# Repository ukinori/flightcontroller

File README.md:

# STM32H743 VTOL Flight Controller

Custom four-layer flight-controller hardware for VTOL and fixed-wing aircraft, designed in **KiCad 10** around the **STM32H743VITx**. The intended aircraft configuration is four lift motors, one cruise motor and up to five servos. The hardware has twelve output connectors, allowing spare channels.

**Status: routed hardware prototype.** PX4 integration is planned; this repository does not contain a completed PX4 board port, bootloader or flight-tested firmware. The board has not been electrically or flight qualified. Design-rule checks do not establish functional or flight safety.

[Hardware inspection guide](docs/PROJECT-RU.md) · [Board review and bring-up checklist](docs/PROJECT-RU.md#before-fabrication-and-bring-up)

Current KiCad 3D rendering. Sensor bodies include nominal package envelopes; see [3D model notes](3d-model-notes.json).

## Hardware

- STM32H743VITx microcontroller, external 8 MHz crystal, SWD and reset/boot access.
- Two ICM-42688-P inertial sensors and one BMI088; BMP390 barometers.
- SPI FRAM and a microSD socket using SDMMC.
- USB-C USB 2.0 device interface with separate CC pull-down resistors and USB protection.
- GPS, telemetry and RC UART connectors; external I2C connectors for compass/airspeed devices.
- Battery-voltage and external current-sense inputs, status indicators, safety input and buzzer circuitry.
- Twelve signal/GND output headers; OUT7–OUT12 also carry a separately supplied servo rail.
- TPS62162DSG fixed 3.3 V buck regulator and a filtered analog supply.
- Approximate board size: 70 × 100 mm; four copper layers; nominal thickness 1.6 mm.

Exact component references, values, connections and footprints are defined by the KiCad sources. The BOM CSV files cover footprint assignments and selected power/crystal/decoupling parts; they are not a fully qualified purchasing BOM.

## Open the project

1. Download the repository or clone it with `git clone https://github.com/ukinori/flightcontroller.git`.
2. Open **flightcontroller.kicad_pro** in KiCad 10.
3. Open **flightcontroller.kicad_sch** for the schematic hierarchy and **flightcontroller.kicad_pcb** for the routed board.
4. Install the standard KiCad symbol and footprint libraries. Project-specific libraries are bundled in **FlightController.kicad_sym** and **FlightController.pretty/** and use `${KIPRJMOD}` paths.
5. In PCB Editor, press **Alt+3** to open the 3D Viewer. Keep `models/` beside the project and install the standard KiCad 3D model libraries.
6. Refill copper zones and rerun ERC/DRC after making changes.

The root schematic contains MCU, power and interface sheets. The MCU sheet is currently named **untitled.kicad_sch**; this file is required by the hierarchy.

## Power connections

- **J4:** regulated **5 V input** for the controller; pin 1 is +5V and pin 2 is GND.
- The intended 6–12S aircraft battery requires a **separate external regulator**. Do not connect raw pack voltage to J4.
- USB VBUS and the external supply feed the controller input through diode paths; the onboard converter produces 3.3 V.
- **J22:** separate regulated **6 V servo supply**; pin 1 is VCC_SERVO and pin 2 is GND. The connector footprint is Phoenix Contact **1715721**.
- Controller and servo grounds are common. Servo power is independent of the 3.3 V logic supply.

The servo distribution has a provisional 10 A aggregate design target, **not a verified current rating**. Select actual servos, calculate combined stall/peak current and validate the BEC, connector, wiring, copper thickness, voltage drop and temperature rise before use. Servos/ESCs must accept the controller's signal levels.

## Output mapping

Every output header uses pin 1 for signal and pin 3 for GND. Pin 2 is unconnected on OUT1–OUT6; on OUT7–OUT12 it is VCC_SERVO.

- OUT1 — J11 — PE9, through R31.
- OUT2 — J10 — PE11, through R33.
- OUT3 — J9 — PE13, through R30.
- OUT4 — J6 — PE14, through R27.
- OUT5 — J5 — PC6, through R26.
- OUT6 — J7 — PC7, through R35.
- OUT7 — J8 — PD12, through R32.
- OUT8 — J12 — PD13, through R28.
- OUT9 — J13 — PD14, through R34.
- OUT10 — J16 — PD15, through R25.
- OUT11 — J15 — PA0, through R29.
- OUT12 — J14 — PA1, through R24.

The intended allocation is OUT1–OUT5 for five DShot ESCs, OUT7–OUT11 for five PWM servos, and OUT6/OUT12 as spares. Timer, DMA and output-mode support still need implementation and testing in a dedicated PX4 board port.

## Other connectors

See the [JST-GH wiring guide](README-JST-GH.md) and [connector BOM](JST-GH-CONNECTORS.csv) before making cables.

- **J1 SWD (custom 5-pin GH):** pin 1 SWDIO, pin 2 SWCLK, pin 3 NRST, pin 4 3.3 V reference, pin 5 GND.
- **J18 GPS (6-pin GH, Pixhawk GPS2 signal order):** pin 1 +5V, pin 2 controller TX, pin 3 controller RX, pin 4 SCL, pin 5 SDA, pin 6 GND.
- **J19 telemetry (6-pin GH):** pin 1 +5V, pin 2 controller TX, pin 3 controller RX, pins 4/5 unconnected, pin 6 GND. Hardware RTS/CTS flow control is unavailable.
- **J17 RC UART (6-pin GH):** pin 1 +5V, pin 2 controller TX, pin 3 controller RX, pins 4/5 unconnected, pin 6 GND. Hardware RTS/CTS flow control is unavailable.
- **J20/J21 external I2C (4-pin GH):** pin 1 **+5V power**, pin 2 SCL, pin 3 SDA, pin 4 GND. Pull-ups and logic remain at 3.3 V. These ports and GPS share the external I2C4 bus.
- **J24 buzzer (2-pin GH):** pin 1 +5V, pin 2 switched buzzer return; intended active buzzer limit 20 mA.
- **J23 sensing (original header retained):** pin 1 battery-voltage sensing input, pin 2 external 0–3.3 V current-sense signal, pin 3 GND. Confirm the divider range against the actual battery and component ratings before connecting it.

J4, J22, OUT1–OUT12, USB-C and microSD remain unchanged. J23 remains a power-measurement exception because the GH voltage rating is 50 V, below a fully charged 12S pack at 50.4 V. RC and SWD retain custom pinouts and are not interchangeable with Pixhawk RC/debug cables.

TX/RX names refer to the controller. Check the external device's voltage levels and cable pinout; matching connector size does not establish compatibility.

## Copper layers

- **F.Cu:** components and signal/power tracks, GND pours and servo-power copper.
- **In1.Cu:** GND plane, without ordinary routed tracks.
- **In2.Cu:** 3.3 V pour plus signal and power routing. It is not an uninterrupted power plane.
- **B.Cu:** signal/power routing plus +5V and VCC_SERVO pours.

Review the final manufacturer's stack-up, signal return paths, USB/SDMMC routing, converter layout and servo-current distribution before fabrication. Current design minima include 0.15 mm tracks/clearances and 0.20 mm via drills; these require manufacturer confirmation.

## Verification snapshot — 2026-10-22

KiCad CLI 10.0.4 checks on the publication snapshot:

- ERC: **0 reported violations**.
- DRC: **0 reported physical violations**.
- Unconnected items: **0**.
- Schematic/PCB parity issues: **0**.

The existing project settings ignore some checks. DRC ignores `missing_courtyard`, `track_not_centered_on_via`, `tuning_profile_track_geometries`, `footprint_filters_mismatch` and `footprint_type_mismatch`. ERC ignores `single_global_label`, `four_way_junction`, `simulation_model_issue` and `footprint_filter`. The JSON reports retain this information. Zero findings apply to this configured check set.

Current JST-GH revision reports are `verification/ERC-2026-10-22.json` and `verification/DRC-2026-10-22.json`. All 480 schematic pin assignments match the board; the 125 unchanged footprints retain their positions. No check severities were relaxed for this revision. Older reports, images and routing notes are retained as historical records.

## Repository contents

- Root KiCad files — flight-controller schematic, PCB and project settings.
- `FlightController.pretty/`, `FlightController.kicad_sym` — project-local CAD libraries.
- CSV/Markdown files — component-selection records, footprint assignments and engineering notes.
- `verification/` — ERC, DRC and net-assignment checks, with dated historical reports.
- `images/flightcontroller-3d.png` — current board rendering.
- `models/` — nominal ICM42688 and BMP390 package envelopes used by KiCad 3D Viewer.
- `README-JST-GH.md`, `JST-GH-CONNECTORS.csv` — current port wiring and connector parts.
- `docs/PROJECT-RU.md` — English hardware inspection and bring-up guide. Legacy filenames containing `RU` are retained for existing links; all current documentation is in English.
- `meshtransciever/` — a separate, unfinished radio/mesh hardware project included from the source folder. Its PCB is a placeholder; it is not part of the flight-controller verification results.

Editor history, restore backups, lock files and machine-specific UI state are excluded. The published project uses a portable symbol-library table with project-relative paths.

## Remaining work

1. Complete schematic, layout, power-budget, thermal, mechanical and BOM review.
2. Select actual servos/BEC and agree the fabrication stack-up and capabilities.
3. Develop the custom PX4 port and bootloader; configure clocks, sensors, buses, ADC, output timers/DMA and sensor orientations.
4. Assemble and bring up a prototype using a current-limited 5 V bench supply, initially without ESCs, servos or propellers.
5. Verify rails, SWD access, clock startup and each peripheral, then test power transients, temperature, vibration, EMC and output behaviour before any aircraft use.

No project-wide license has been added. Existing third-party library notices are retained in their source files.

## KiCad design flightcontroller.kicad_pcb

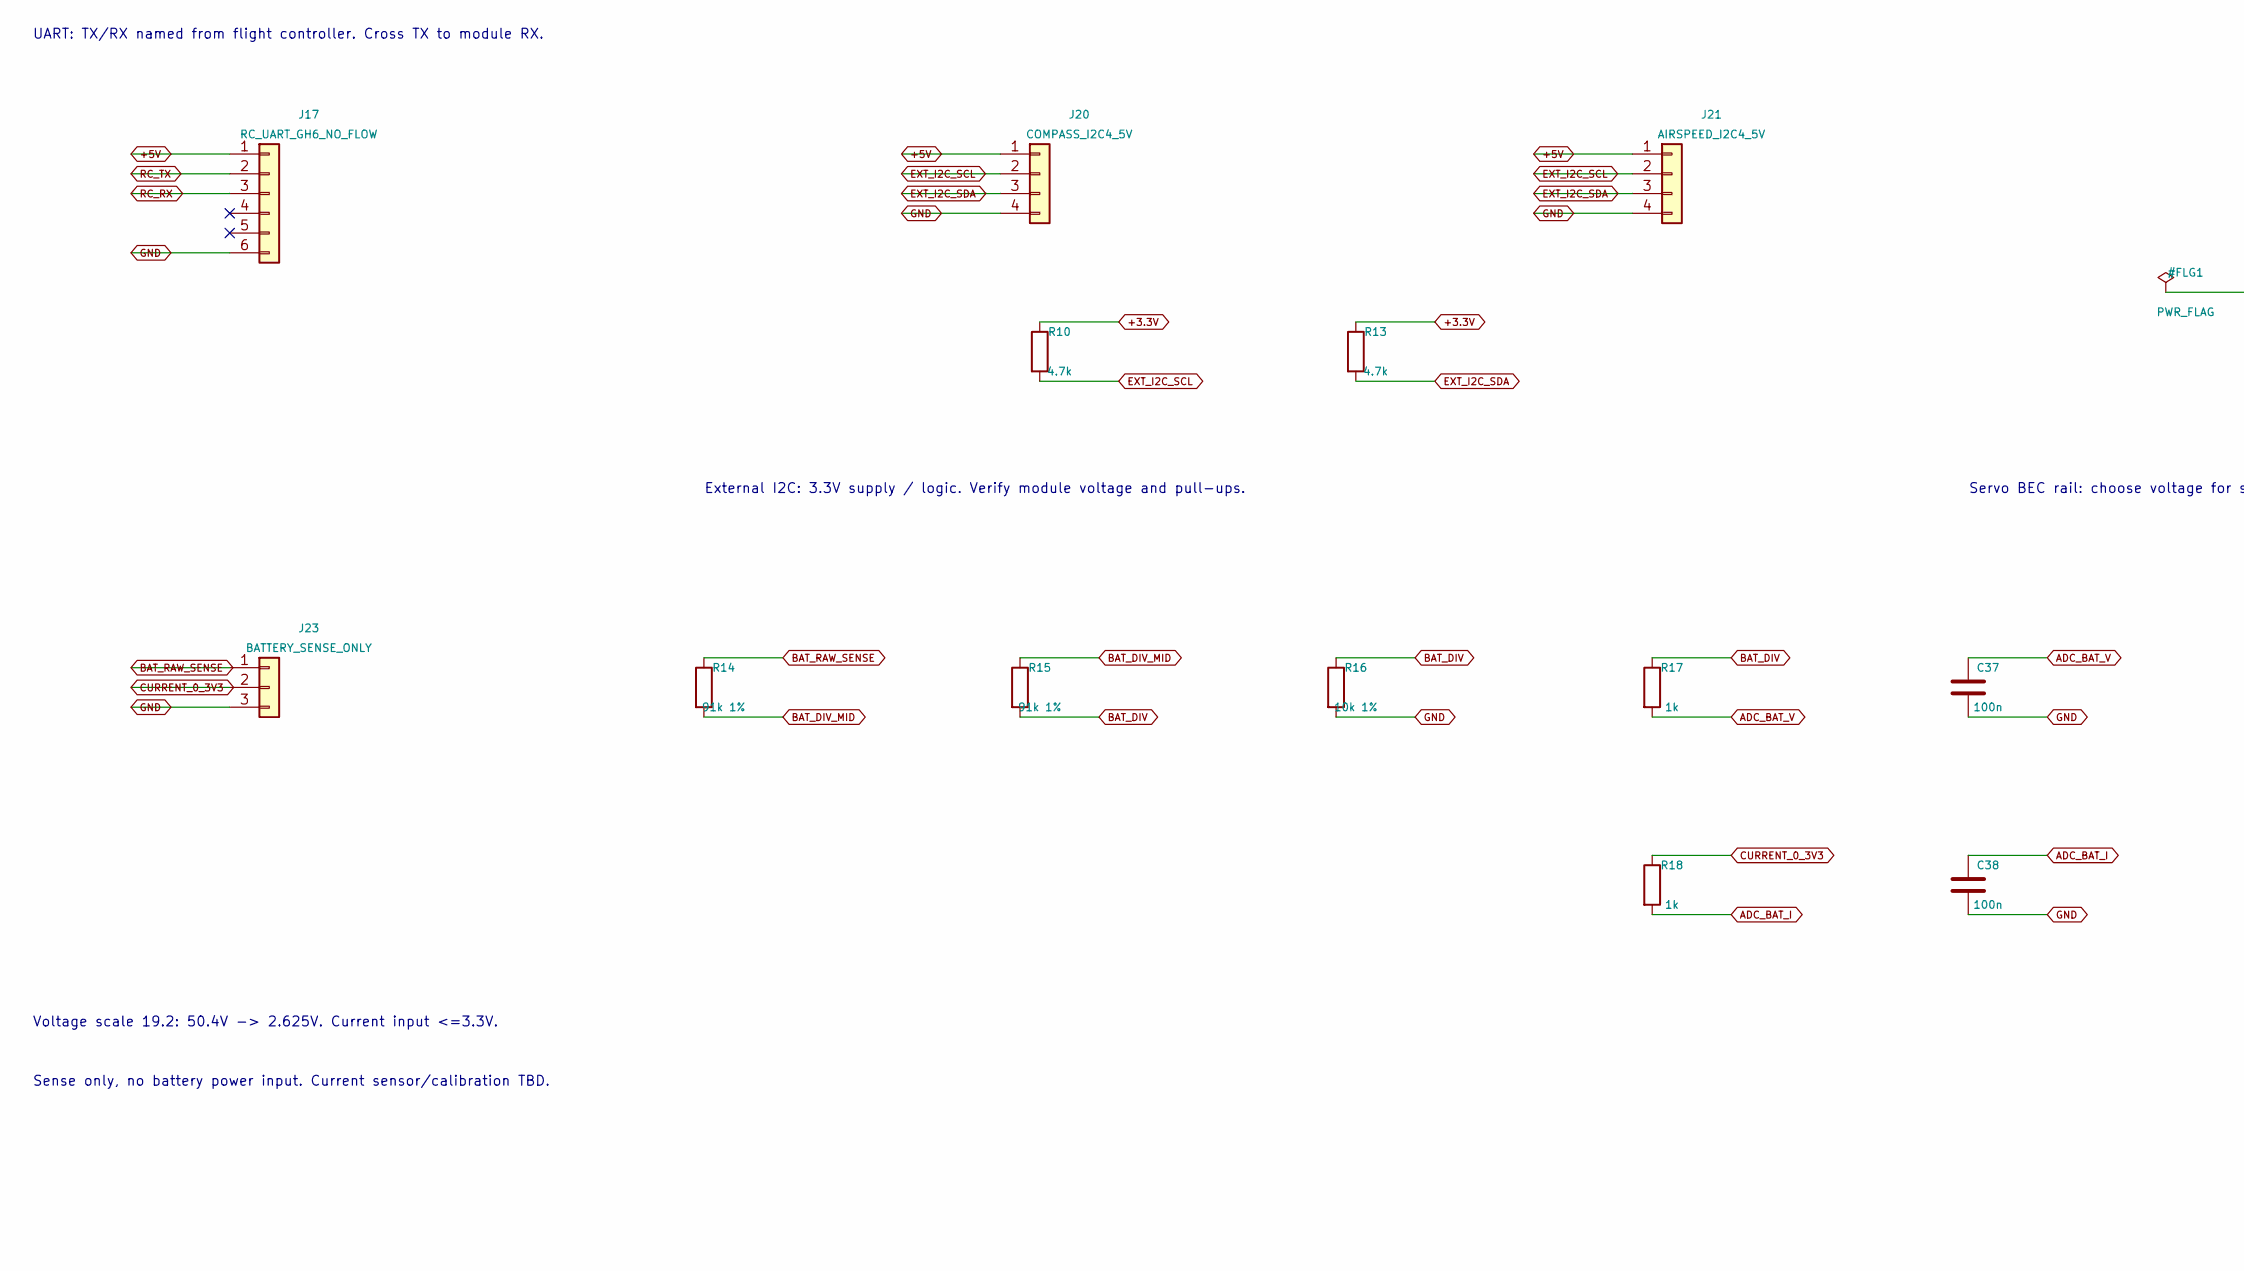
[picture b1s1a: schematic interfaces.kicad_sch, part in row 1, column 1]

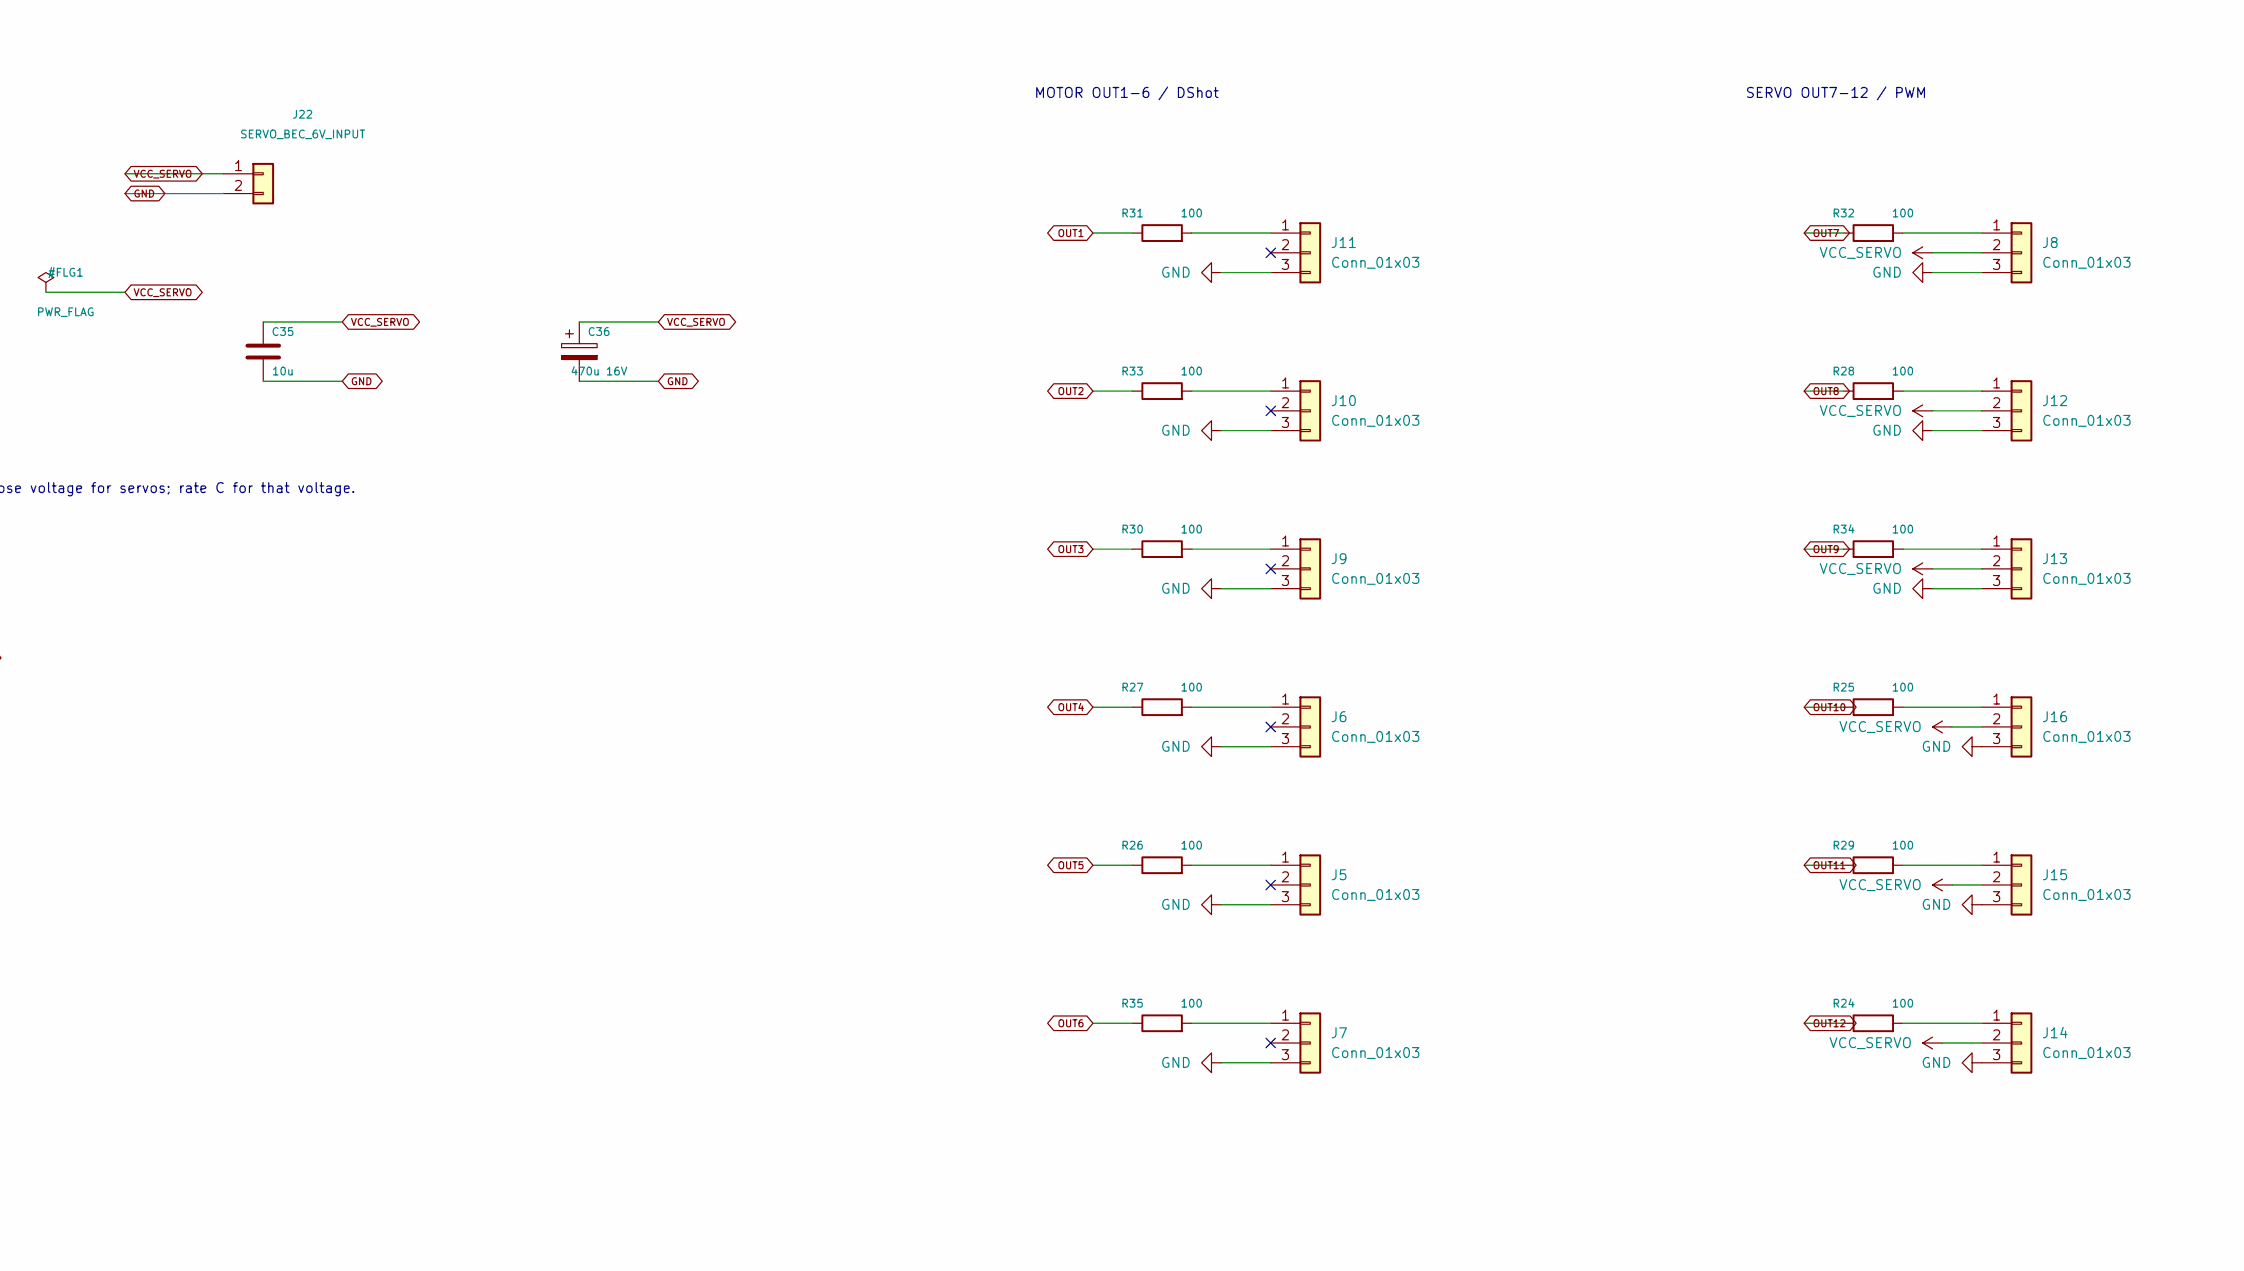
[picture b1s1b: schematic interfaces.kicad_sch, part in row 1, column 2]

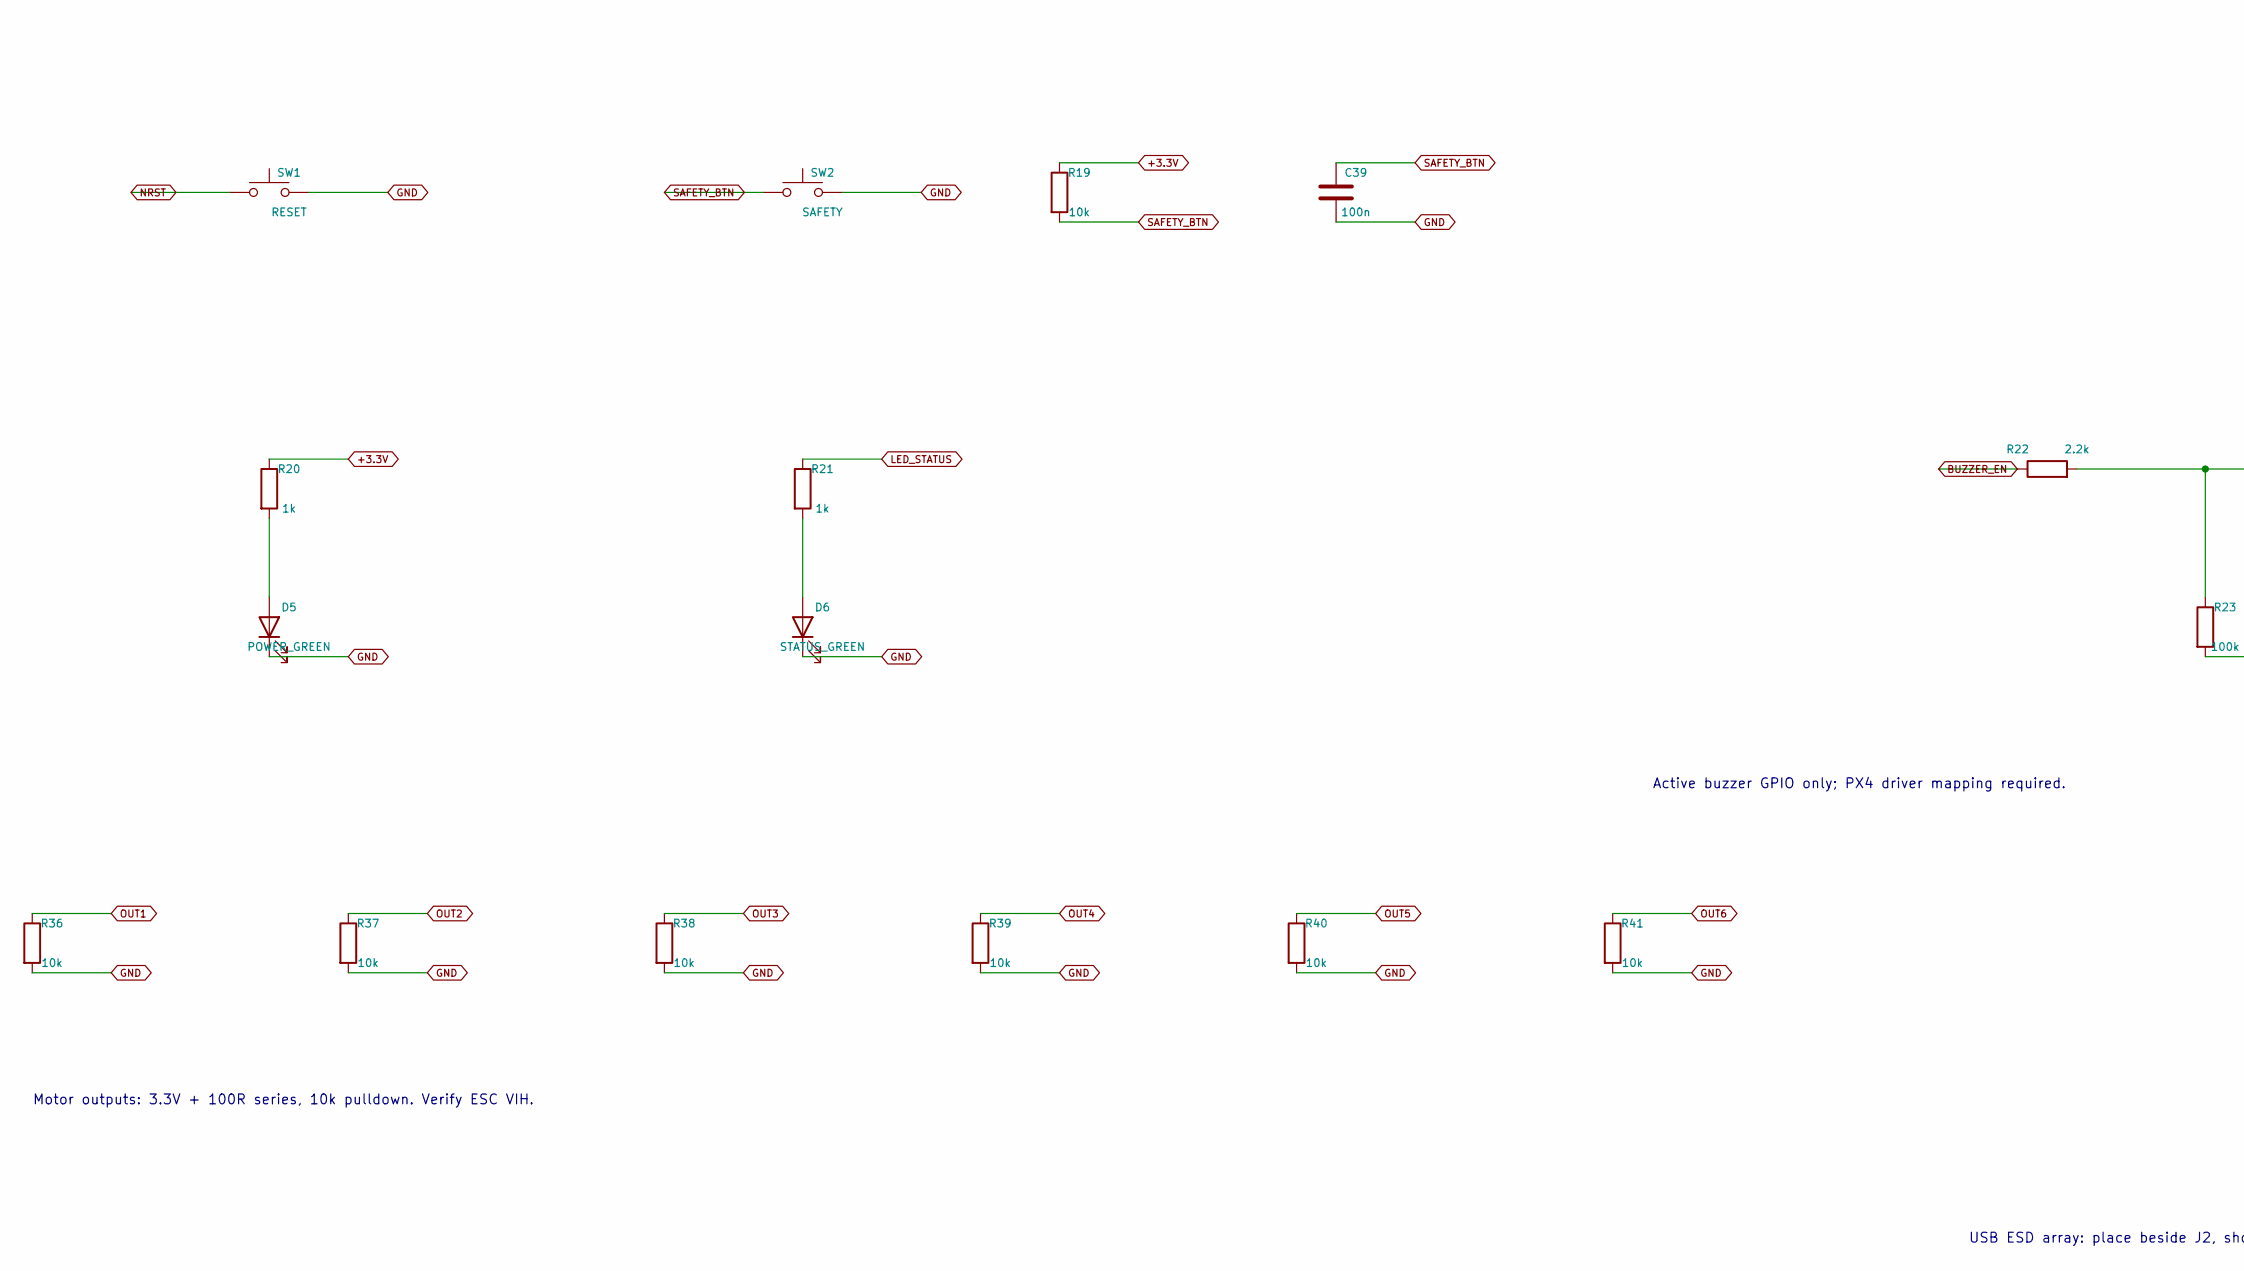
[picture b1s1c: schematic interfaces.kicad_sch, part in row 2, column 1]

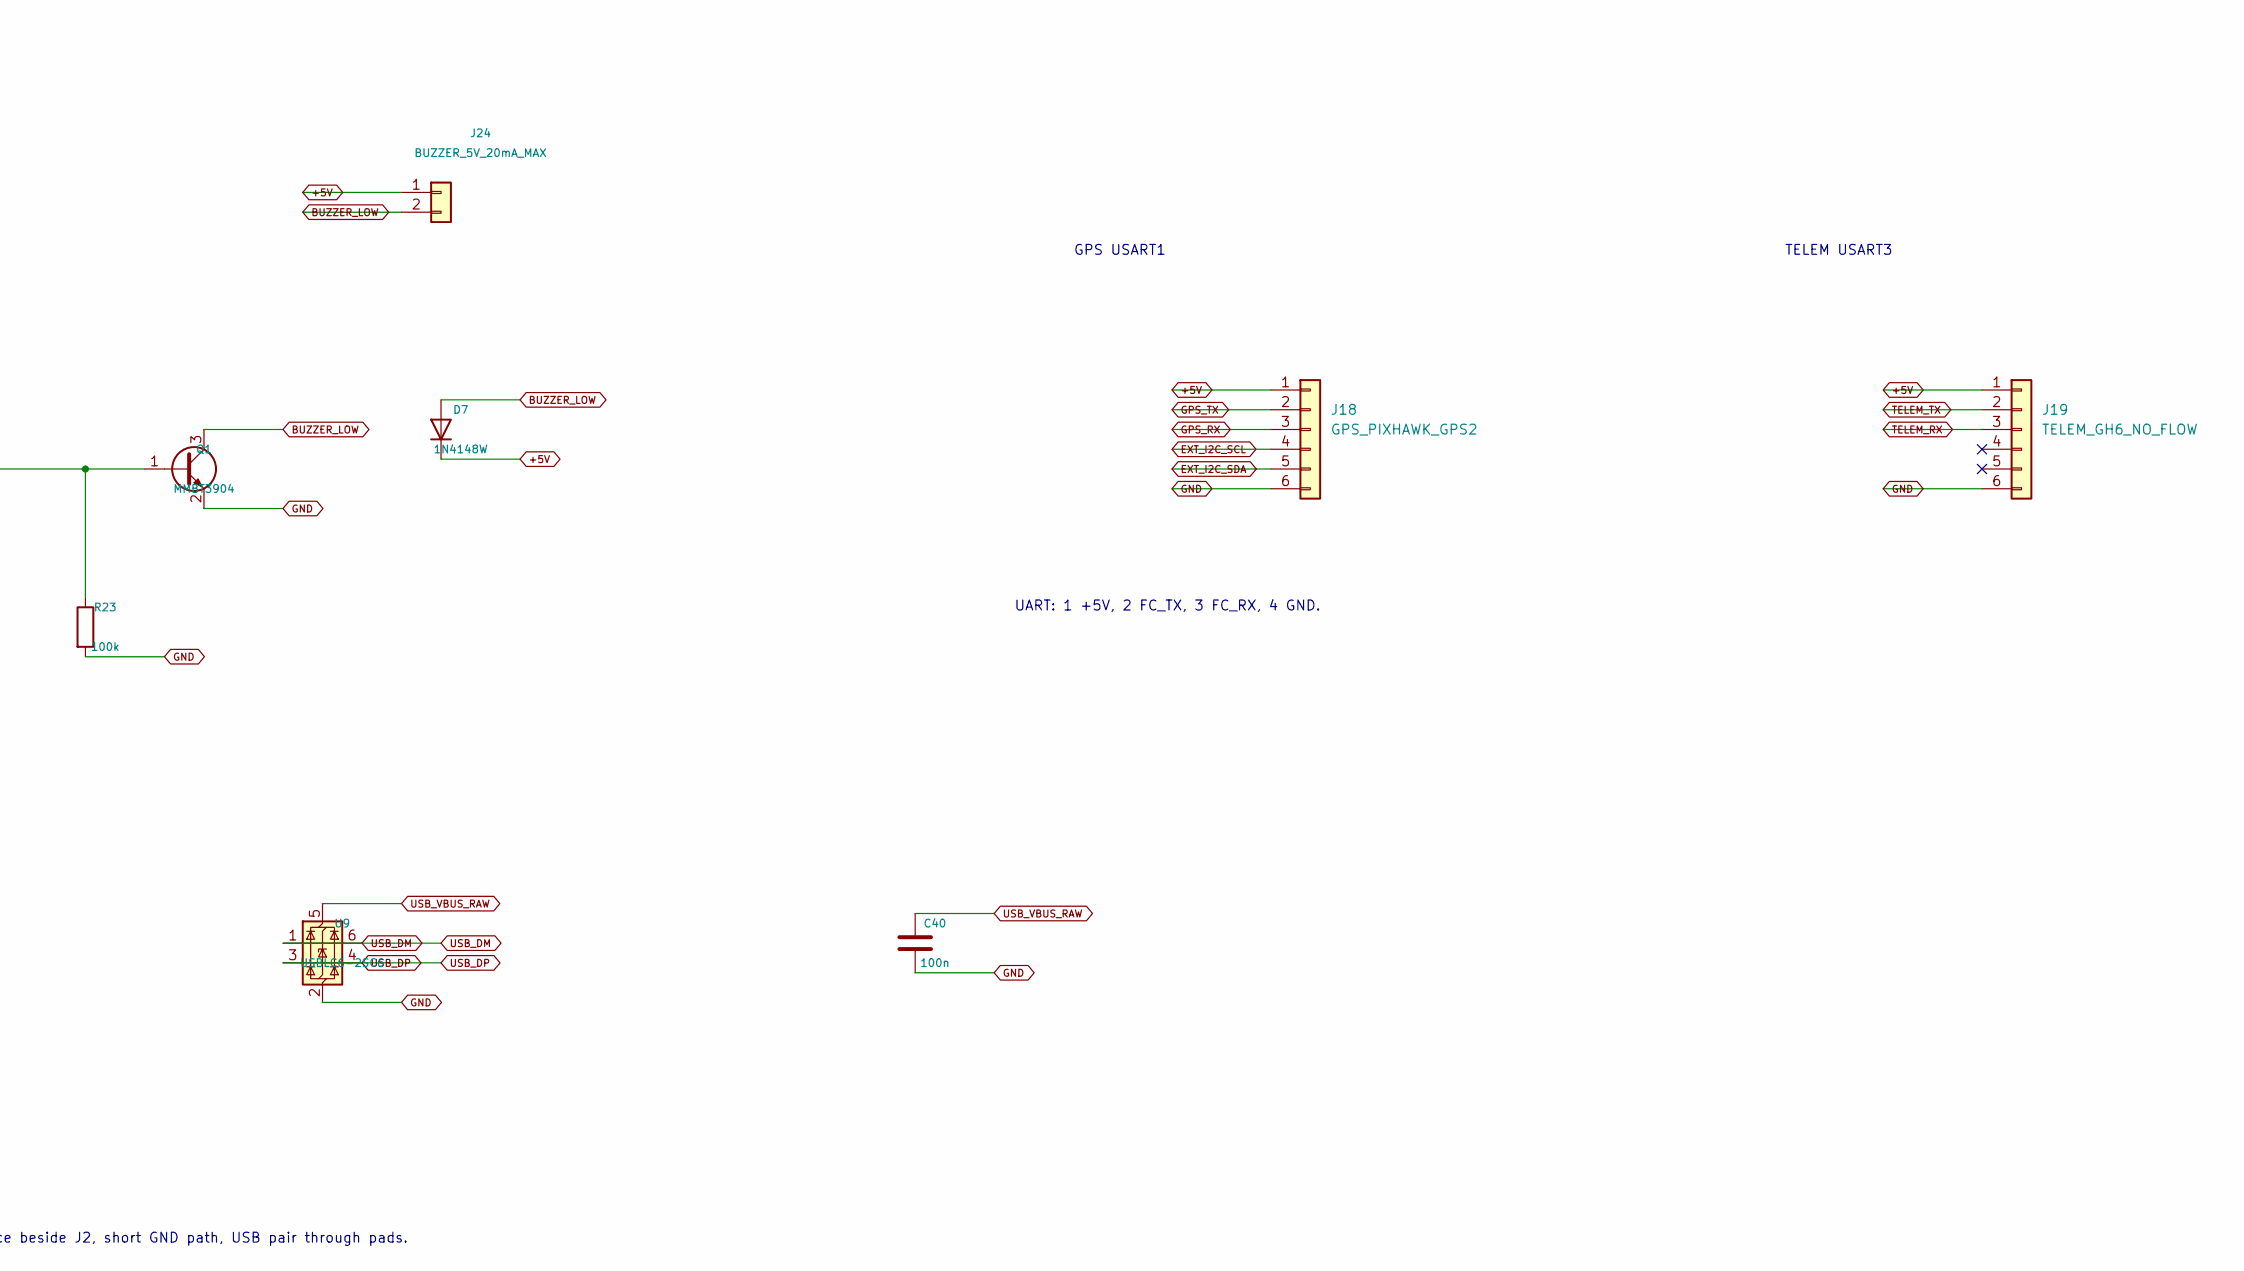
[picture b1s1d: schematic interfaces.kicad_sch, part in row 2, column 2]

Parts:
C35: 10u; C_0603_1608Metric
C36: 470u 16V; CP_Radial_D8.0mm_P3.50mm
C37, C38, C39, C40: 100n; C_0603_1608Metric
D5: POWER_GREEN; LED_0603_1608Metric
D6: STATUS_GREEN; LED_0603_1608Metric
D7: 1N4148W; D_SOD-123
J5, J6, J7, J8, J9, J10, J11, J12, J13, J14, J15, J16: Conn_01x03; PinHeader_1x03_P2.54mm_Vertical
J17: RC_UART_GH6_NO_FLOW; JST_GH_SM06B-GHS-TB_1x06-1MP_P1.25mm_Horizontal
J18: GPS_PIXHAWK_GPS2; JST_GH_SM06B-GHS-TB_1x06-1MP_P1.25mm_Horizontal
J19: TELEM_GH6_NO_FLOW; JST_GH_SM06B-GHS-TB_1x06-1MP_P1.25mm_Horizontal
J20: COMPASS_I2C4_5V; JST_GH_SM04B-GHS-TB_1x04-1MP_P1.25mm_Horizontal
J21: AIRSPEED_I2C4_5V; JST_GH_SM04B-GHS-TB_1x04-1MP_P1.25mm_Horizontal
J22: SERVO_BEC_6V_INPUT; TerminalBlock_Phoenix_MKDS-1,5-2-5.08_1x02_P5.08mm_Horizont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; MPN 1715721
J23: BATTERY_SENSE_ONLY; PinHeader_1x03_P2.54mm_Vertical
J24: BUZZER_5V_20mA_MAX; JST_GH_SM02B-GHS-TB_1x02-1MP_P1.25mm_Horizontal
Q1: MMBT3904; SOT-23
R10, R13: 4.7k; R_0603_1608Metric
R14, R15: 91k 1%; R_0603_1608Metric
R16: 10k 1%; R_0603_1608Metric
R17, R18, R20, R21: 1k; R_0603_1608Metric
R19, R36, R37, R38, R39, R40, R41: 10k; R_0603_1608Metric
R22: 2.2k; R_0603_1608Metric
R23: 100k; R_0603_1608Metric
R24, R25, R26, R27, R28, R29, R30, R31, R32, R33, R34, R35: 100; R_0603_1608Metric
SW1: RESET; SW_SPST_TL3342
SW2: SAFETY; SW_SPST_TL3342
U9: USBLC6-2SC6; SOT-23-6

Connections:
+3.3V: R10.1, R13.1, R19.1, R20.1; also elsewhere on the board
+5V: D7.1 (K), J17.1, J18.1, J19.1, J20.1, J21.1, J24.1; also elsewhere on the board
ADC_BAT_I: C38.1, R18.2; also elsewhere on the board
ADC_BAT_V: C37.1, R17.2; also elsewhere on the board
BAT_DIV: R15.2, R16.1, R17.1
BAT_DIV_MID: R14.2, R15.1
BAT_RAW_SENSE: J23.1, R14.1
BUZZER_EN: R22.1; also elsewhere on the board
BUZZER_LOW: D7.2 (A), J24.2, Q1.3 (C)
CURRENT_0_3V3: J23.2, R18.1
EXT_I2C_SCL: J18.4, J20.2, J21.2, R10.2; also elsewhere on the board
EXT_I2C_SDA: J18.5, J20.3, J21.3, R13.2; also elsewhere on the board
GND: C35.2, C36.2, C37.2, C38.2, C39.2, C40.2, D5.1 (K), D6.1 (K), J5.3, J6.3, J7.3, J8.3, J9.3, J10.3, J11.3, J12.3, J13.3, J14.3, J15.3, J16.3, J17.6, J18.6, J19.6, J20.4, J21.4, J22.2, J23.3, Q1.2 (E), R16.2, R23.2, R36.2, R37.2, R38.2, R39.2, R40.2, R41.2, SW1.2, SW2.2, U9.2 (GND); also elsewhere on the board
GPS_RX: J18.3; also elsewhere on the board
GPS_TX: J18.2; also elsewhere on the board
LED_STATUS: R21.1; also elsewhere on the board
NRST: SW1.1; also elsewhere on the board
unnamed: D5.2 (A), R20.2
unnamed: D6.2 (A), R21.2
unnamed: J5.1, R26.2
unnamed: J6.1, R27.2
unnamed: J7.1, R35.2
unnamed: J8.1, R32.2
unnamed: J9.1, R30.2
unnamed: J10.1, R33.2
unnamed: J11.1, R31.2
unnamed: J12.1, R28.2
unnamed: J13.1, R34.2
unnamed: J14.1, R24.2
unnamed: J15.1, R29.2
unnamed: J16.1, R25.2
unnamed: Q1.1 (B), R22.2, R23.1
OUT1: R31.1, R36.1; also elsewhere on the board
OUT2: R33.1, R37.1; also elsewhere on the board
OUT3: R30.1, R38.1; also elsewhere on the board
OUT4: R27.1, R39.1; also elsewhere on the board
OUT5: R26.1, R40.1; also elsewhere on the board
OUT6: R35.1, R41.1; also elsewhere on the board
OUT7: R32.1; also elsewhere on the board
OUT8: R28.1; also elsewhere on the board
OUT9: R34.1; also elsewhere on the board
OUT10: R25.1; also elsewhere on the board
OUT11: R29.1; also elsewhere on the board
OUT12: R24.1; also elsewhere on the board
RC_RX: J17.3; also elsewhere on the board
RC_TX: J17.2; also elsewhere on the board
SAFETY_BTN: C39.1, R19.2, SW2.1; also elsewhere on the board
TELEM_RX: J19.3; also elsewhere on the board
TELEM_TX: J19.2; also elsewhere on the board
USB_DM: U9.1 (I/O1), U9.6 (I/O1); also elsewhere on the board
USB_DP: U9.3 (I/O2), U9.4 (I/O2); also elsewhere on the board
USB_VBUS_RAW: C40.1, U9.5 (VBUS); also elsewhere on the board
VCC_SERVO: C35.1, C36.1, J8.2, J12.2, J13.2, J14.2, J15.2, J16.2, J22.1

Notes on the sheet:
External I2C: 3.3V supply / logic. Verify module voltage and pull-ups.
Motor outputs: 3.3V + 100R series, 10k pulldown. Verify ESC VIH.
UART: TX/RX named from flight controller. Cross TX to module RX.
GPS USART1
Voltage scale 19.2: 50.4V -> 2.625V. Current input <=3.3V.
UART: 1 +5V, 2 FC_TX, 3 FC_RX, 4 GND.
TELEM USART3
SERVO OUT7-12 / PWM
Servo BEC rail: choose voltage for servos; rate C for that voltage.
USB ESD array: place beside J2, short GND path, USB pair through pads.
Sense only, no battery power input. Current sensor/calibration TBD.
Active buzzer GPIO only; PX4 driver mapping required.
MOTOR OUT1-6 / DShot

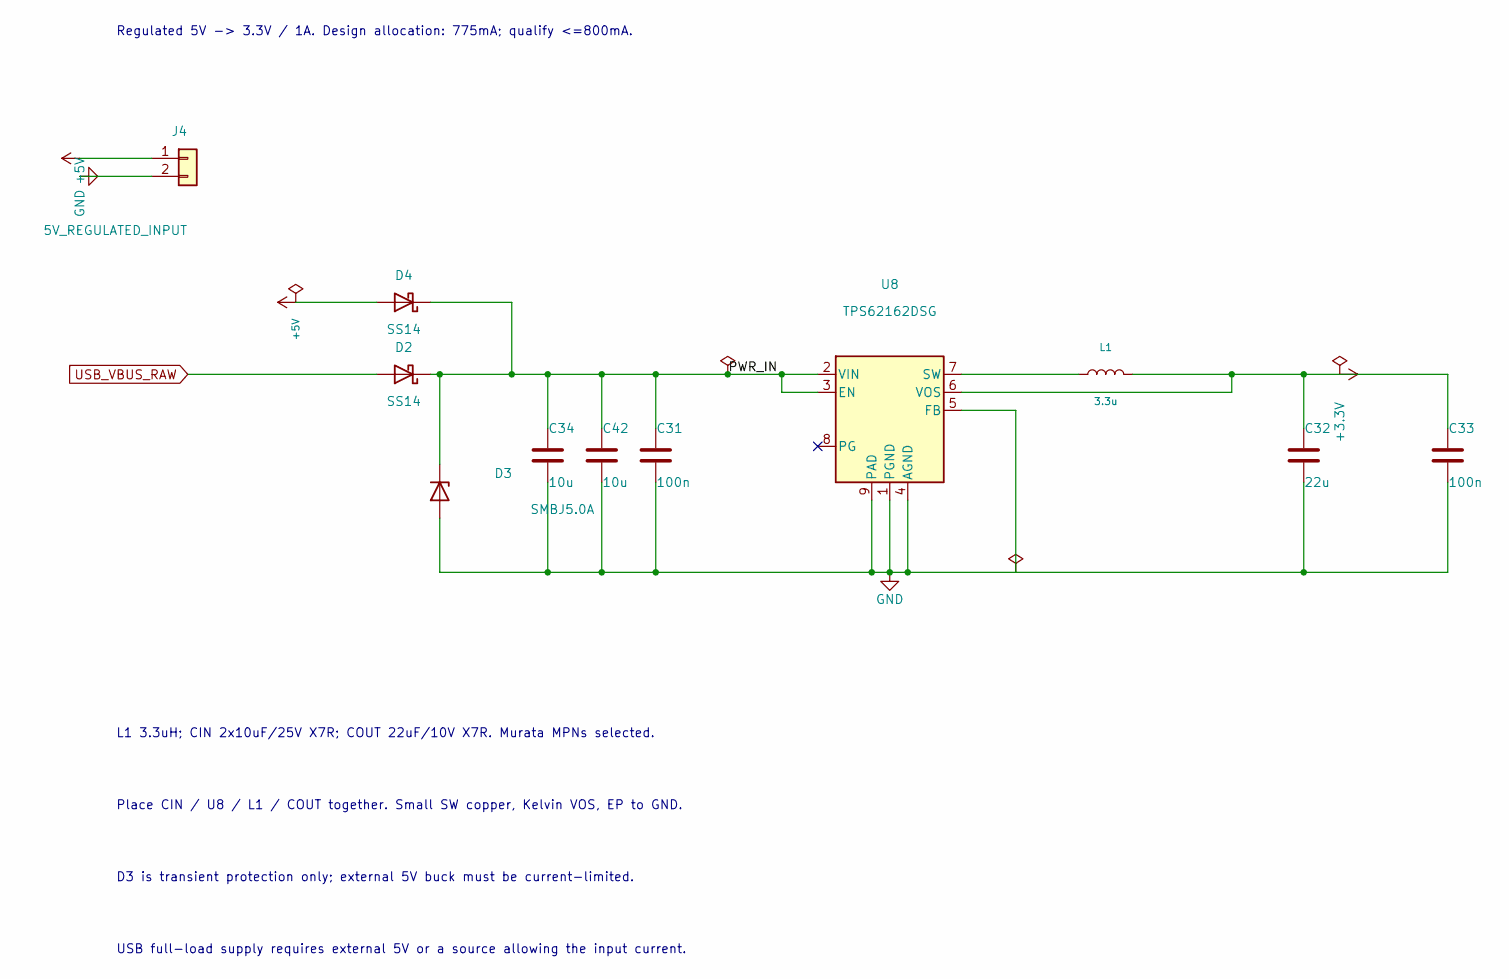
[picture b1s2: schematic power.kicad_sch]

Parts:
C31, C33: 100n; C_0603_1608Metric; Voltage 25V; Tolerance 10%; MPN GRM188R71E104KA01D
C32: 22u; C_1206_3216Metric; Voltage 10V; Tolerance 10%; MPN GRM31CR71A226KE15L
C34, C42: 10u; C_1206_3216Metric; Voltage 25V; Tolerance 10%; MPN GRM31CR71E106KA12L
D2, D4: SS14; D_SMA
D3: SMBJ5.0A; D_SMB; MPN SMBJ5.0A-E3/52
J4: 5V_REGULATED_INPUT; PinHeader_1x02_P2.54mm_Vertical
L1: 3.3u; L_Coilcraft_XAL4030-XXX; MPN XAL4030-332MEC
U8: TPS62162DSG; WSON-8-1EP_2x2mm_P0.5mm_EP0.9x1.6mm_ThermalVias; MPN TPS62162DSGR

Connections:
+3.3V: C32.1, C33.1, L1.2, U8.6 (VOS); also elsewhere on the board
+5V: D4.2 (A), J4.1; also elsewhere on the board
/power/PWR_IN: C31.1, C34.1, C42.1, D2.1 (K), D3.1 (K), D4.1 (K), U8.2 (VIN), U8.3 (EN)
GND: C31.2, C32.2, C33.2, C34.2, C42.2, D3.2 (A), J4.2, U8.1 (PGND), U8.4 (AGND), U8.5 (FB), U8.9 (PAD); also elsewhere on the board
unnamed: L1.1, U8.7 (SW)
USB_VBUS_RAW: D2.2 (A); also elsewhere on the board

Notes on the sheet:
Place CIN / U8 / L1 / COUT together. Small SW copper, Kelvin VOS, EP to GND.
L1 3.3uH; CIN 2x10uF/25V X7R; COUT 22uF/10V X7R. Murata MPNs selected.
USB full-load supply requires external 5V or a source allowing the input current.
Regulated 5V -> 3.3V / 1A. Design allocation: 775mA; qualify <=800mA.
D3 is transient protection only; external 5V buck must be current-limited.
